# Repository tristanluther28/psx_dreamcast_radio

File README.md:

# PlayStation & Dreamcast Radio Controller!
More to come: Pardon our dust

https://tristanluther.com/projects/psx_dream_radio/

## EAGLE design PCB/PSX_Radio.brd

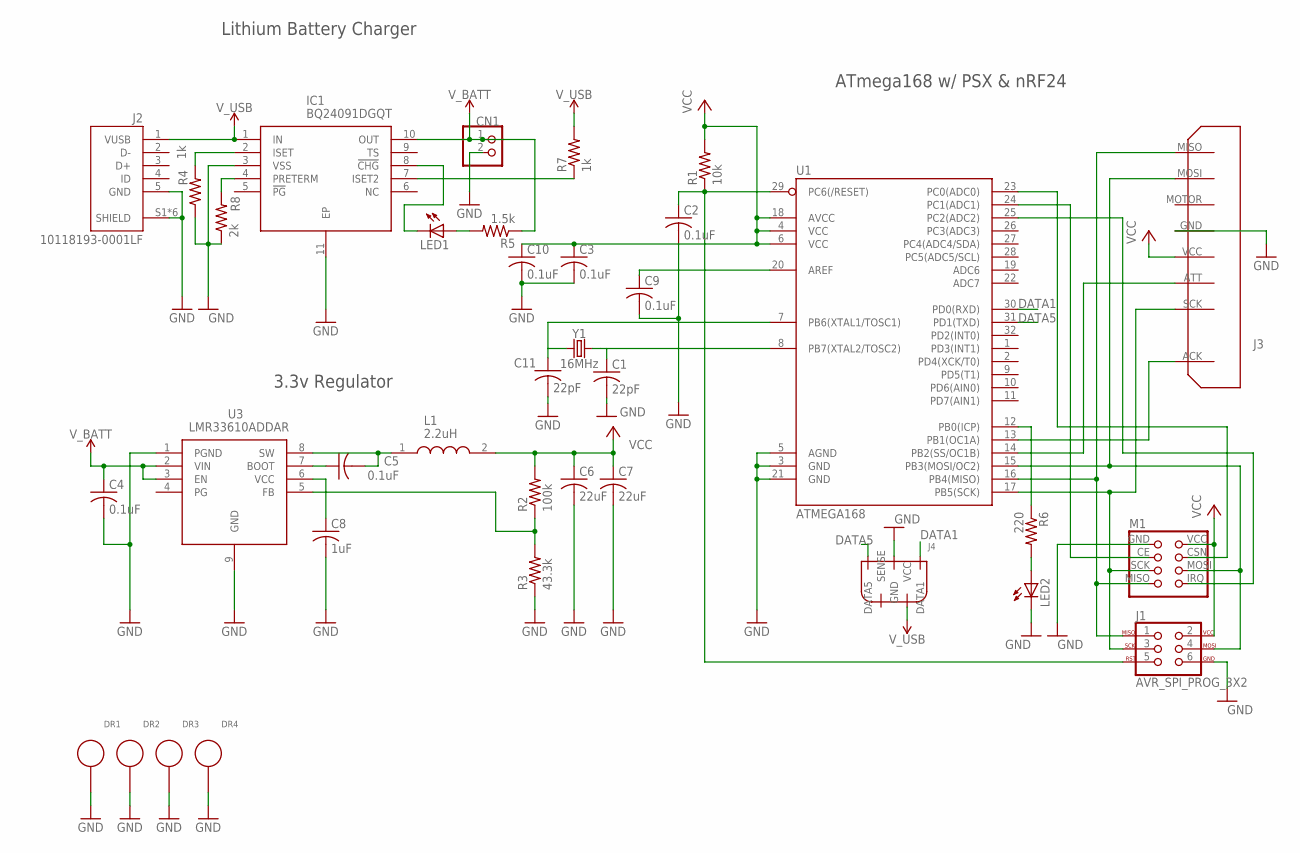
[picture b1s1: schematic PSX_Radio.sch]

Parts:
C1, C11: 22pF; C0805
C2, C3, C4, C5, C9, C10: 0.1uF; C0805
C6, C7: 22uF; C0805
C8: 1uF; C0805
CN1: JST_2PIN-SMT-RA; JST-PH-2-SMT-RA
DR1, DR2, DR3, DR4: 3MM_DRILL_GND
IC1: BQ24091DGQT; SOP50P490X110-11N
J1: AVR_SPI_PROG_3X2; 2X3-NS
J2: 10118193-0001LF; FCI_10118193-0001LF
J3: PSX_CONTROLLER; PSX_VERTICAL
J4: DREAMCAST_CONTROLLER; 1X06
L1: 2.2uH; INDPM5752X150N
LED1, LED2: LED5MM
M1: NRF24L01_MODULE; 2X04
R1: 10k; R0805
R2: 100k; R0805
R3: 43.3k; R0805
R4, R7: 1k; R0805
R5: 1.5k; R0805
R6: 220; R0805
R8: 2k; R0805
U1: ATMEGA168; TQFP32-08
U3: LMR33610ADDAR; SOIC127P600X170-9N
Y1: 16MHz; CRYSTAL-SMD-5X3.2-4PAD

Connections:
DATA1: J4.2 (DATA1), U1.30 (PD0(RXD))
DATA5: J4.4 (DATA5), U1.31 (PD1(TXD))
GND: C1.2, C2.2, C3.2, C4.2, C6.2, C7.2, C8.2, C9.2, C10.2, C11.2, CN1.2 (1), DR1.DR, DR2.DR, DR3.DR, DR4.DR, IC1.3 (VSS), IC1.11 (EP), J1.6, J2.5 (GND), J2.S1 (SHIELD), J2.S2 (SHIELD), J2.S3 (SHIELD), J2.S4 (SHIELD), J2.S5 (SHIELD), J2.S6 (SHIELD), J3.GND, J4.5 (GND), LED2.K (C), M1.GND, R3.1, R4.1, R8.1, U1.3 (GND), U1.5 (AGND), U1.21 (GND), U3.1 (PGND), U3.9 (GND)
unnamed: J1.1, J3.MISO, M1.MISO, U1.16 (PB4(MISO))
unnamed: J1.4, J3.MOSI, M1.MOSI, U1.15 (PB3(MOSI/OC2))
unnamed: J3.ACK, U1.13 (PB1(OC1A))
unnamed: M1.IRQ, U1.25 (PC2(ADC2))
unnamed: J1.3, J3.SCK, M1.SCK, U1.17 (PB5(SCK))
unnamed: M1.CE, U1.24 (PC1(ADC1))
unnamed: J3.ATT, U1.14 (PB2(SS/OC1B))
unnamed: M1.CSN, U1.23 (PC0(ADC0))
unnamed: C2.1, J1.5, R1.1, U1.29 (PC6(/RESET))
unnamed: C9.1, U1.20 (AREF)
unnamed: C5.1, U3.7 (BOOT)
unnamed: C5.2, L1.1, U3.8 (SW)
unnamed: IC1.2 (ISET), R4.2
unnamed: R2.1, R3.2, U3.5 (FB)
unnamed: C8.1, U3.6 (VCC)
unnamed: R6.1, U1.12 (PB0(ICP))
unnamed: LED2.A, R6.2
unnamed: C1.1, U1.8 (PB7(XTAL2/TOSC2)), Y1.3 (2)
unnamed: C11.1, U1.7 (PB6(XTAL1/TOSC1)), Y1.1
unnamed: LED1.A, R5.2
unnamed: IC1.8 (!CHG), LED1.K (C)
unnamed: IC1.7 (ISET2), R7.1
unnamed: IC1.4 (PRETERM), R8.2
VCC: C3.1, C6.1, C7.1, C10.1, J1.2, J3.VCC, L1.2, M1.VCC, R1.2, R2.2, U1.4 (VCC), U1.6 (VCC), U1.18 (AVCC)
V_BATT: C4.1, CN1.1 (2), IC1.10 (OUT), R5.1, U3.2 (VIN), U3.3 (EN)
V_USB: IC1.1 (IN), J2.1 (VUSB), J4.1 (VCC), R7.2

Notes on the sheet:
Lithium Battery Charger
3.3v Regulator
ATmega168 w/ PSX & nRF24

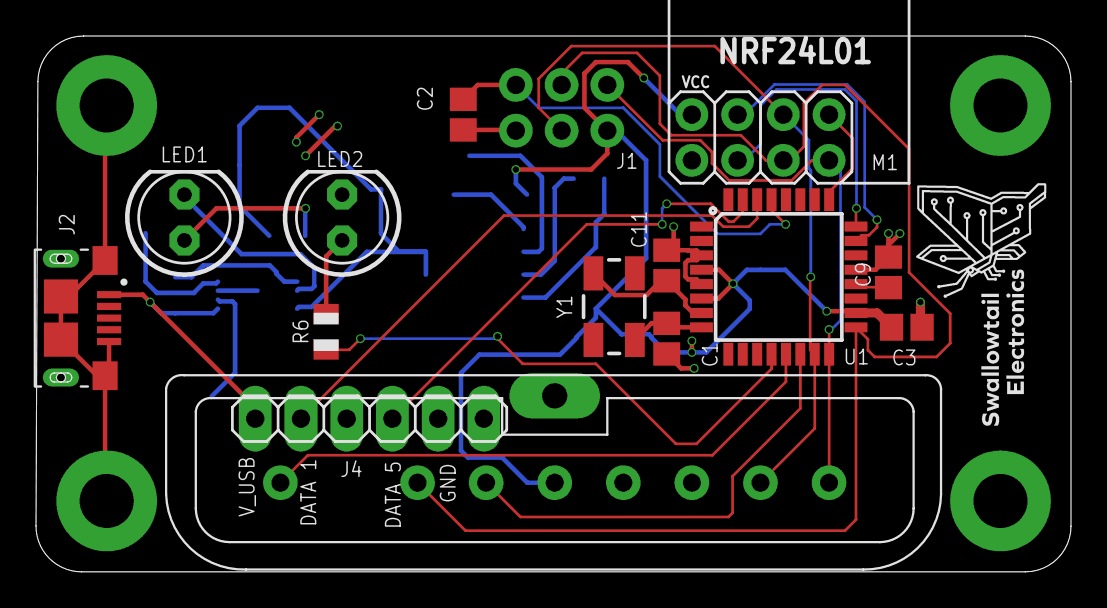
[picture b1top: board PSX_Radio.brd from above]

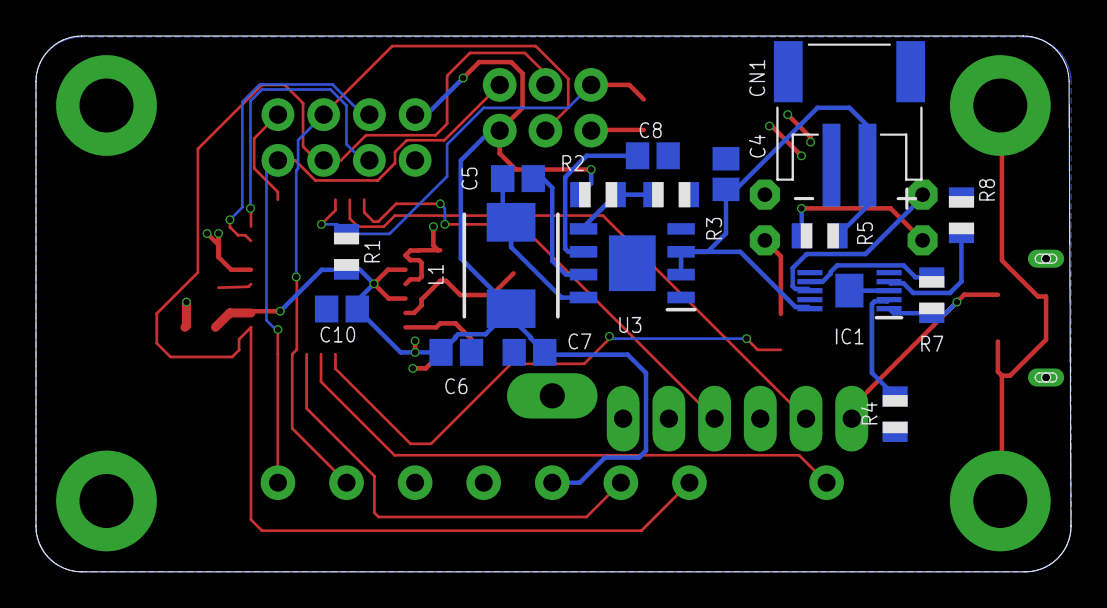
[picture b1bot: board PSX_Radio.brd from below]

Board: 2 copper layers, 57.5 x 29.8 mm, 37 parts (17 on the bottom side), 29 nets.

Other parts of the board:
U$3: SWALLOWTAIL_LOGO_SMALL

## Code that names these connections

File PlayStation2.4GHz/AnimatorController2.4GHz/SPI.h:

  
  //-----------------------------------------------------------------------------
  //
  //  SPI_ATmega328P.h
  //
  //  Swallowtail SPI Firmware
  //  AVR (ATmega328P) SPI Firmware
  //
  //  Copyright (c) 2021 Swallowtail Electronics
  //
  //  Permission is hereby granted, free of charge, to any person obtaining a
  //  copy of this software and associated documentation files (the "Software"),
  //  to deal in the Software without restriction, including without limitation
  //  the rights to use, copy, modify, merge, publish, distribute, sub-license,
  //  and/or sell copies of the Software, and to permit persons to whom the
  //  Software is furnished to do so, subject to the following conditions:
  //
  //  The above copyright notice and this permission notice shall be included in
  //  all copies or substantial portions of the Software.
  //
  //  THE SOFTWARE IS PROVIDED "AS IS", WITHOUT WARRANTY OF ANY KIND, EXPRESS OR
  //  IMPLIED, INCLUDING BUT NOT LIMITED TO THE WARRANTIES OF MERCHANTABILITY,
  //  FITNESS FOR A PARTICULAR PURPOSE AND NONINFRINGEMENT. IN NO EVENT SHALL THE
  //  AUTHORS OR COPYRIGHT HOLDERS BE LIABLE FOR ANY CLAIM, DAMAGES OR OTHER
  //  LIABILITY, WHETHER IN AN ACTION OF CONTRACT, TORT OR OTHERWISE, ARISING
  //  FROM, OUT OF OR IN CONNECTION WITH THE SOFTWARE OR THE USE OR OTHER
  //  DEALINGS IN THE SOFTWARE.
  //
  //  Web:    http://tristanluther.com
  //  Email:  tristanluther28@gmail.com
  //
  //-----------------------------------------------------------------------------

  /******************** Macros *****************************/

  #define SS PB2
  #define MOSI PB3
  #define MISO PB4
  #define SCK PB5
  #define DDR_SPI DDRB
  #define PORT_SPI PORTB
  #define BIT_SET(byte, bit) (byte & (1<<bit))

  /******************** Includes ***************************/

  #include <avr/io.h>

  /******************* Globals *****************************/


  /******************** Functions **************************/

  //Initialize the USI on the ATmega168/328 for Three-Wire Operation
  void SPI_init(){
	  //Initialize the output for SPI Master Mode
	  DDR_SPI |= (1<<SS)|(1<<MOSI)|(0<<MISO)|(1<<SCK); //SS | MOSI | MISO | SCK
	  //Set the default values for outputs to zero and inputs to have pull-up resistors
	  PORT_SPI |= (0<<SS)|(0<<MOSI)|(1<<MISO)|(0<<SCK); //SS | MOSI | MISO | SCK
	  //SPI Control Register, Enable, MSB bit first, Set to master mode, Mode 0:0, f/128 SCK Frequency
	  SPCR = (1<<SPE) | (1<<DORD) | (1<<MSTR) | (1<<CPOL) | (1<<CPHA) | (0<<SPR1) | (1<<SPR0);
	  SPSR = (0<<SPI2X);
	  return; //Return to call point
  }

  //Enable the slave select line
  void SPI_Enable(){
	  //Enable SS Line
	  PORT_SPI &= ~(1<<SS);
  }

  //Enable the slave select line
  void SPI_Disable(){
	  //Disable SS Line
	  PORT_SPI |= (1<<SS);
  }

  //Writes the byte into the device
  uint8_t SPI_Transfer(uint8_t byte){
	  //Write data to SPI register
	  SPDR = byte;
	  //Wait until the transmission is complete
	  while(!(SPSR & (1<<SPIF)));
	  //Return the data in the register
	  return SPDR;
  }

  /******************** Interrupt Service Routines *********/

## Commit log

2021-08-06 Initial commit
    Putting everything in one place
2021-08-06 Added README.md
    temp

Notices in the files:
parts and their libraries:
SparkFun-PowerSymbols: Licensing: Creative Commons ShareAlike 4.0 International - https://creativecommons.org/licenses/by-sa/4.0
